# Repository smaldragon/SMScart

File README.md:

# SMScart

A wip discrete logic cart for the sega master system, with partial sega mapper compatibility:

* ROM must be <=512Kb
* ROM must only use slot 2 banking
* ROM must not have extra on-board ram
* ROM must not have save functionality

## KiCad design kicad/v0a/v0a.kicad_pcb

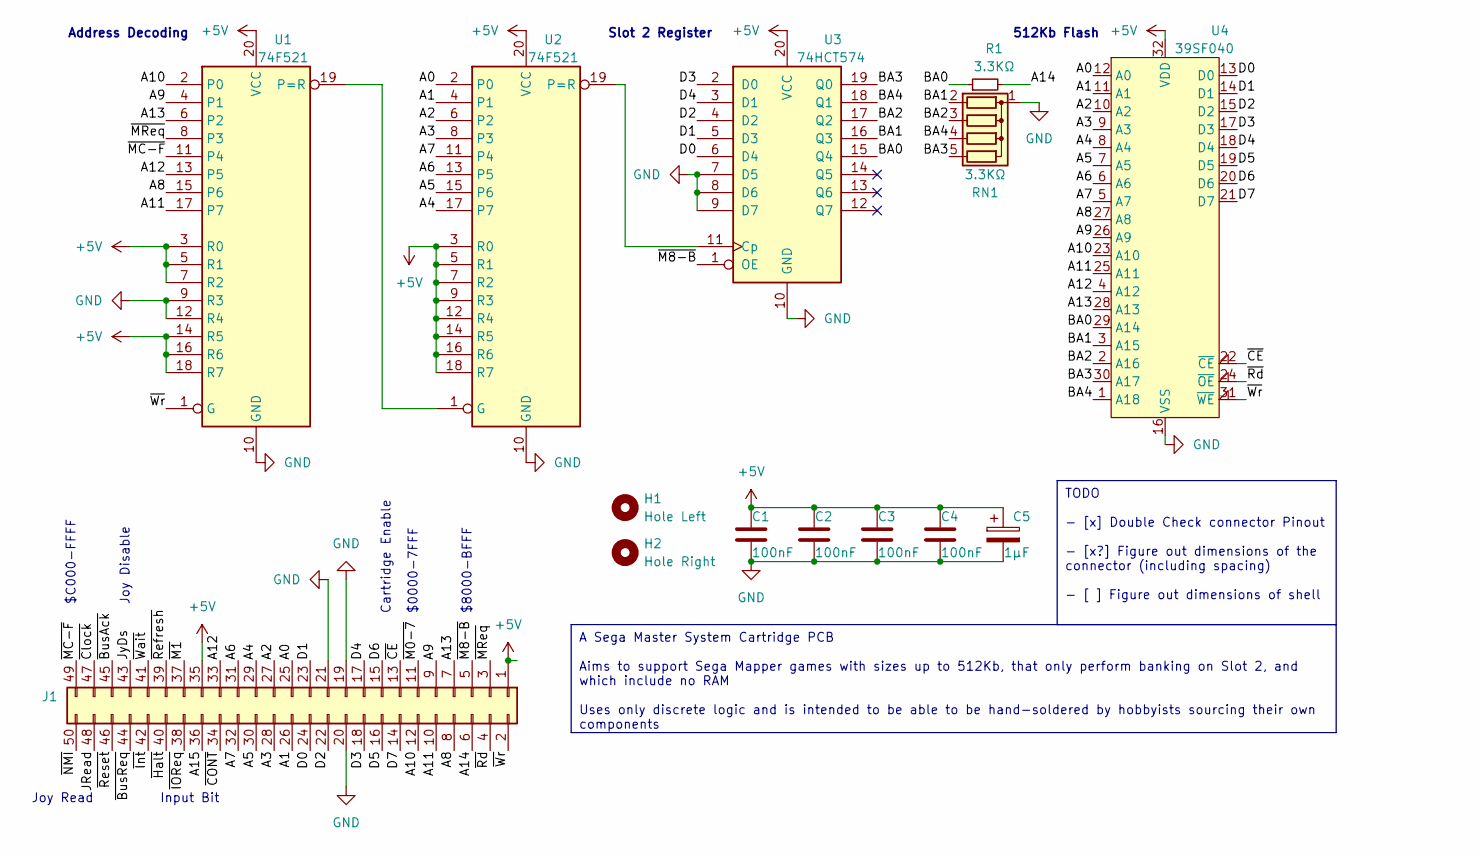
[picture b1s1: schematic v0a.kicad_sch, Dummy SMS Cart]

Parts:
C1, C2, C3, C4: 100nF; C_Disc_D3.0mm_W1.6mm_P2.50mm
C5: 1µF; CP_Radial_D5.0mm_P2.50mm
H1: Hole Left; MountingHole_5mm
H2: Hole Right; MountingHole_5mm
J1: Conn_02x25_Odd_Even; SMS_Cart_Edge
R1: 3.3KΩ; R_Axial_DIN0204_L3.6mm_D1.6mm_P5.08mm_Horizontal
RN1: 3.3KΩ; R_Array_SIP5
U1, U2: 74F521; DIP-20_W7.62mm_Socket_LongPads
U3: 74HCT574; DIP-20_W7.62mm_Socket_LongPads
U4: 39SF040; PLCC-32_SMD-Socket_HandSolder

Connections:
+5V: C1.1, C2.1, C3.1, C4.1, C5.1, J1.1, J1.35, U1.3 (R0), U1.5 (R1), U1.7 (R2), U1.14 (R5), U1.16 (R6), U1.18 (R7), U1.20 (VCC), U2.3 (R0), U2.5 (R1), U2.7 (R2), U2.9 (R3), U2.12 (R4), U2.14 (R5), U2.16 (R6), U2.18 (R7), U2.20 (VCC), U3.20 (VCC), U4.32 (VDD)
/ ~CONT: J1.34
/ ~Reset: J1.46
/A0: J1.25, U2.2 (P0), U4.12 (A0)
/A1: J1.26, U2.4 (P1), U4.11 (A1)
/A2: J1.27, U2.6 (P2), U4.10 (A2)
/A3: J1.28, U2.8 (P3), U4.9 (A3)
/A4: J1.29, U2.17 (P7), U4.8 (A4)
/A5: J1.30, U2.15 (P6), U4.7 (A5)
/A6: J1.31, U2.13 (P5), U4.6 (A6)
/A7: J1.32, U2.11 (P4), U4.5 (A7)
/A8: J1.8, U1.15 (P6), U4.27 (A8)
/A9: J1.9, U1.4 (P1), U4.26 (A9)
/A10: J1.12, U1.2 (P0), U4.23 (A10)
/A11: J1.10, U1.17 (P7), U4.25 (A11)
/A12: J1.33, U1.13 (P5), U4.4 (A12)
/A13: J1.7, U1.6 (P2), U4.28 (A13)
/A14: J1.6, R1.2
/A15: J1.36
/BA0: R1.1, U3.15 (Q4), U4.29 (A14)
/BA1: RN1.2 (R1), U3.16 (Q3), U4.3 (A15)
/BA2: RN1.3 (R2), U3.17 (Q2), U4.2 (A16)
/BA3: RN1.5 (R4), U3.19 (Q0), U4.30 (A17)
/BA4: RN1.4 (R3), U3.18 (Q1), U4.1 (A18)
/D0: J1.24, U3.6 (D4), U4.13 (D0)
/D1: J1.23, U3.5 (D3), U4.14 (D1)
/D2: J1.22, U3.4 (D2), U4.15 (D2)
/D3: J1.18, U3.2 (D0), U4.17 (D3)
/D4: J1.17, U3.3 (D1), U4.18 (D4)
/D5: J1.16, U4.19 (D5)
/D6: J1.15, U4.20 (D6)
/D7: J1.14, U4.21 (D7)
/JRead: J1.48
/JyDs: J1.43
/~BusAck: J1.45
/~BusReq: J1.44
/~CE: J1.13, U4.22 (~CE)
/~Clock: J1.47
/~Halt: J1.40
/~IOReq: J1.38
/~Int: J1.42
/~M0-7: J1.11
/~M1: J1.37
/~M8-B: J1.5, U3.1 (OE)
/~MC-F: J1.49, U1.11 (P4)
/~MReq: J1.3, U1.8 (P3)
/~NMI: J1.50
/~Rd: J1.4, U4.24 (~OE)
/~Refresh: J1.39
/~Wait: J1.41
/~Wr: J1.2, U1.1 (G), U4.31 (~WE)
GND: C1.2, C2.2, C3.2, C4.2, C5.2, J1.19, J1.20, J1.21, RN1.1 (common), U1.9 (R3), U1.10 (GND), U1.12 (R4), U2.10 (GND), U3.7 (D5), U3.8 (D6), U3.9 (D7), U3.10 (GND), U4.16 (VSS)
unnamed: U1.19 (P=R), U2.1 (G)
unnamed: U2.19 (P=R), U3.11 (Cp)

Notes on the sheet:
A Sega Master System Cartridge PCB Aims to support Sega Mapper games with sizes up to 512Kb, that only perform banking on Slot 2, and which include no RAM Uses only discrete logic and is intended to be able to be hand-soldered by hobbyists sourcing their own components
TODO - [x] Double Check connector Pinout - [x?] Figure out dimensions of the connector (including spacing) - [ ] Figure out dimensions of shell
Address Decoding
Cartridge Enable
$8000-BFFF
$0000-7FFF
$C000-FFFF
512Kb Flash
Input Bit
Joy Disable
Joy Read
Slot 2 Register

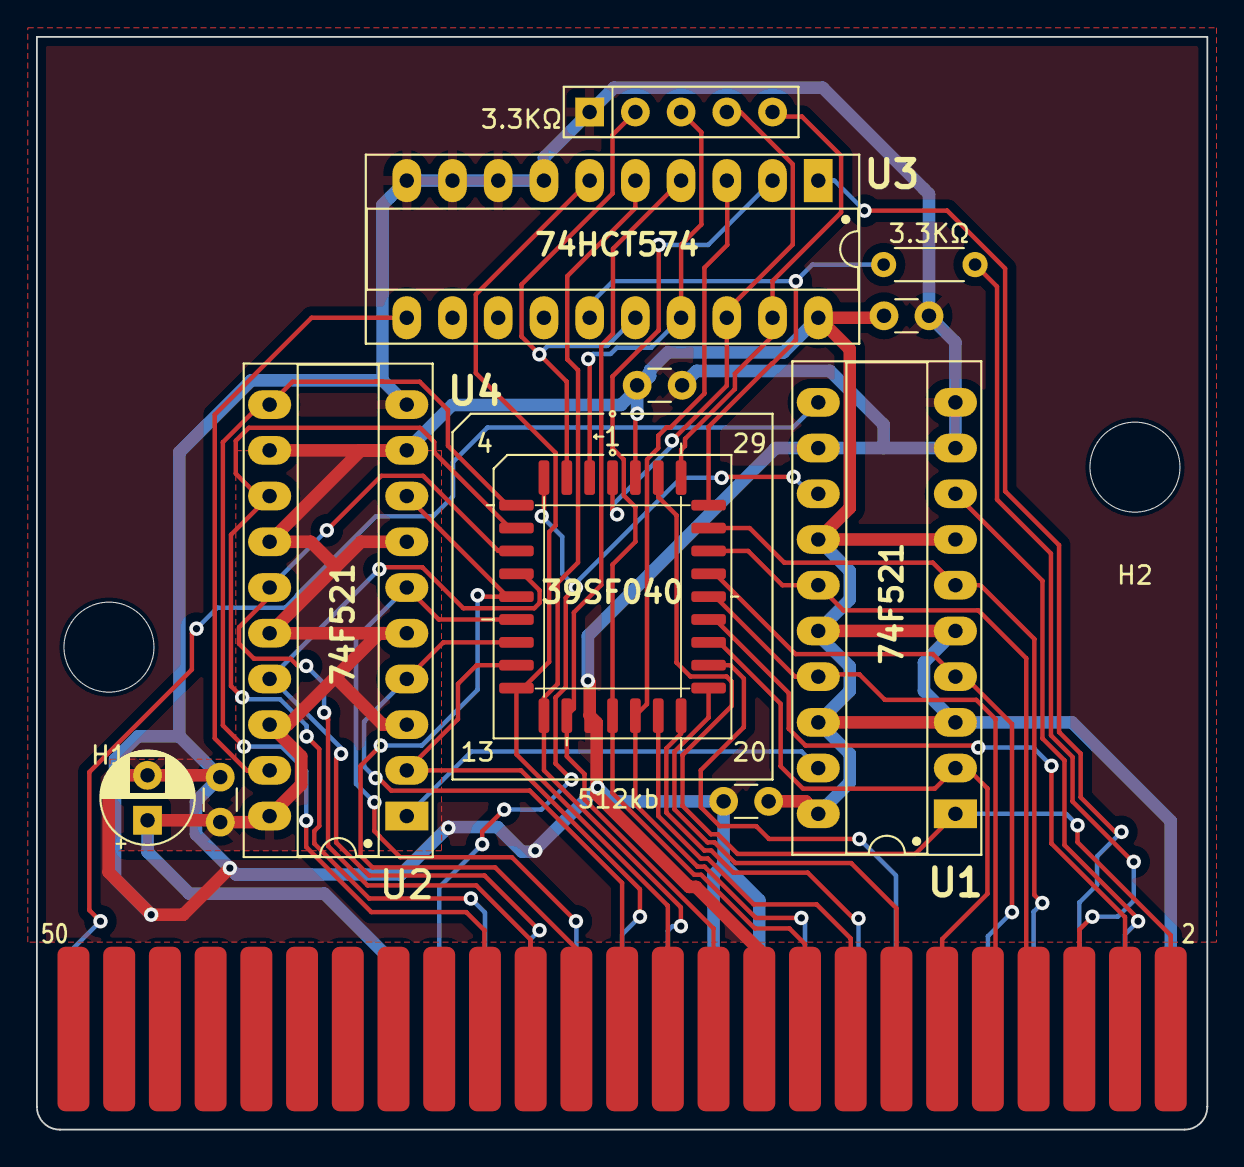
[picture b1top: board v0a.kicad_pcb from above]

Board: 2 copper layers, 65.0 x 60.7 mm, 14 parts (0 on the bottom side), 38 nets.

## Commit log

2023-12-26 Add kicad files
